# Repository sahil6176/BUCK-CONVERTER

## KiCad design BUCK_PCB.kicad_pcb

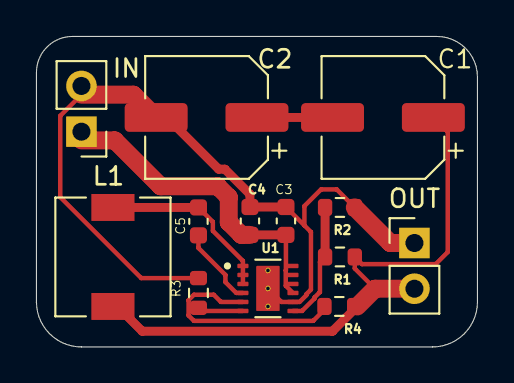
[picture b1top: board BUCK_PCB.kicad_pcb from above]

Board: 2 copper layers, 24.5 x 17.2 mm, 13 parts (0 on the bottom side), 9 nets.

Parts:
C1, C2: 47uF; CP_Elec_6.3x4.9
C3: 10uF; C_0603_1608Metric
C4, C5: 100nF; C_0603_1608Metric
IN: Conn_01x02_Pin; PinHeader_1x02_P2.54mm_Vertical
L1: L; L_6.3x6.3_H3
OUT: Conn_01x02_Pin; PinHeader_1x02_P2.54mm_Vertical
R1, R4: 100k; R_0603_1608Metric
R2: 11.8k; R_0603_1608Metric
R3: 30.9k; R_0603_1608Metric
U1: LMR51450FNDRRR; CONV_LMR51450FNDRRR

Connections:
GND: C2.2, C3.2, C4.2, IN.2, OUT.1, R2.2, R3.2, U1.8 (AGND), U1.13 (PGND), U1.15
unnamed: C1.2, C2.1
unnamed: C5.2, L1.1, U1.1 (SW), U1.2 (SW), U1.3 (SW)
unnamed: C3.1, C4.1, IN.1, U1.9 (EN), U1.10 (VIN), U1.11 (VIN), U1.12 (VIN)
unnamed: C1.1, L1.2, OUT.2, R1.1, R4.2
unnamed: C5.1, U1.4 (BOOT)
unnamed: R1.2, R2.1, U1.7 (FB)
unnamed: R4.1, U1.5 (PG)
unnamed: R3.1, U1.6 (RT)

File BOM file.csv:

"Reference","Qty","Value","DNP","Exclude from BOM","Exclude from Board","Footprint","Datasheet"
"C1,C2","2","47uF","","","","Capacitor_SMD:CP_Elec_6.3x4.9","~"
"C3","1","10uF","","","","Capacitor_SMD:C_0603_1608Metric","~"
"C4,C5","2","100nF","","","","Capacitor_SMD:C_0603_1608Metric","~"
"J1,J2","2","Conn_01x02_Pin","","","","Connector_PinHeader_2.54mm:PinHeader_1x02_P2.54mm_Vertical","~"
"L1","1","4.7uH","","","","Inductor_SMD:L_6.3x6.3_H3","~"
"R1,R4","2","100k","","","","Resistor_SMD:R_0603_1608Metric","~"
"R2","1","11.8k","","","","Resistor_SMD:R_0603_1608Metric","~"
"R3","1","30.9k","","","","Resistor_SMD:R_0603_1608Metric","~"
"U1","1","LMR51450FNDRRR","","","","LMR51450:CONV_LMR51450FNDRRR",""

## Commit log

2025-09-14 MEDIA
